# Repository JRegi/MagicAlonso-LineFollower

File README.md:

# MagicAlonso - _Robot dedicado a la leyenda Asturiana del automobilismo_

## MagicAlonso V1 (sin turbina)

## Descripción

_MagicAlonso_ es un robot seguidor de líneas de alto rendimiento con tracción y succión brushless.

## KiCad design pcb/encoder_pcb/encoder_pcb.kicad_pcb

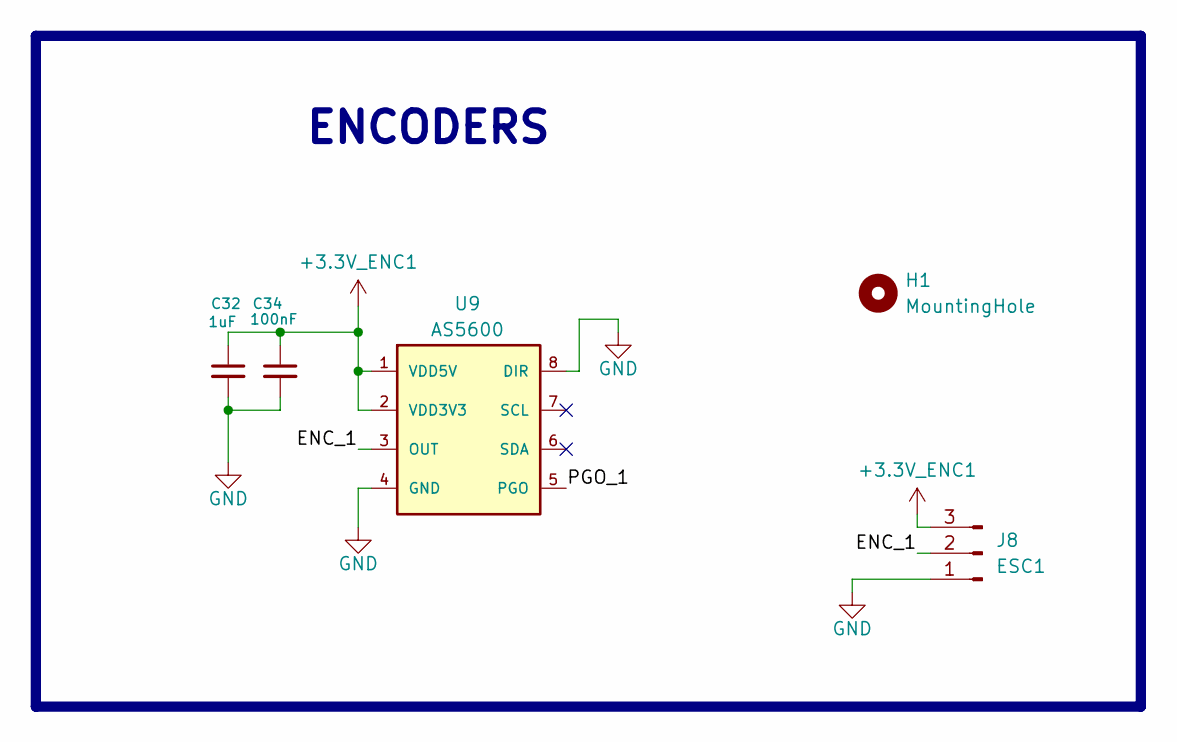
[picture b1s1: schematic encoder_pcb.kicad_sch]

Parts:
C32: 1uF; C_0603_1608Metric
C34: 100nF; C_0603_1608Metric
H1: MountingHole; MountingHole_2.2mm_M2
J8: ESC1; PinHeader_1x03_P2.54-SMD,THT,2-layers
U9: AS5600; SOIC-8_3.9x4.9mm_P1.27mm

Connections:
+3.3V_ENC1: C32.1, C34.1, J8.3, U9.1 (VDD5V), U9.2 (VDD3V3)
/ENC_1: J8.2, U9.3 (OUT)
/PGO_1: U9.5 (PGO)
GND: C32.2, C34.2, J8.1, U9.4 (GND), U9.8 (DIR)

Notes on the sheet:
ENCODERS

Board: 2 copper layers, 5 parts (0 on the bottom side), 3 nets, no tracks yet.

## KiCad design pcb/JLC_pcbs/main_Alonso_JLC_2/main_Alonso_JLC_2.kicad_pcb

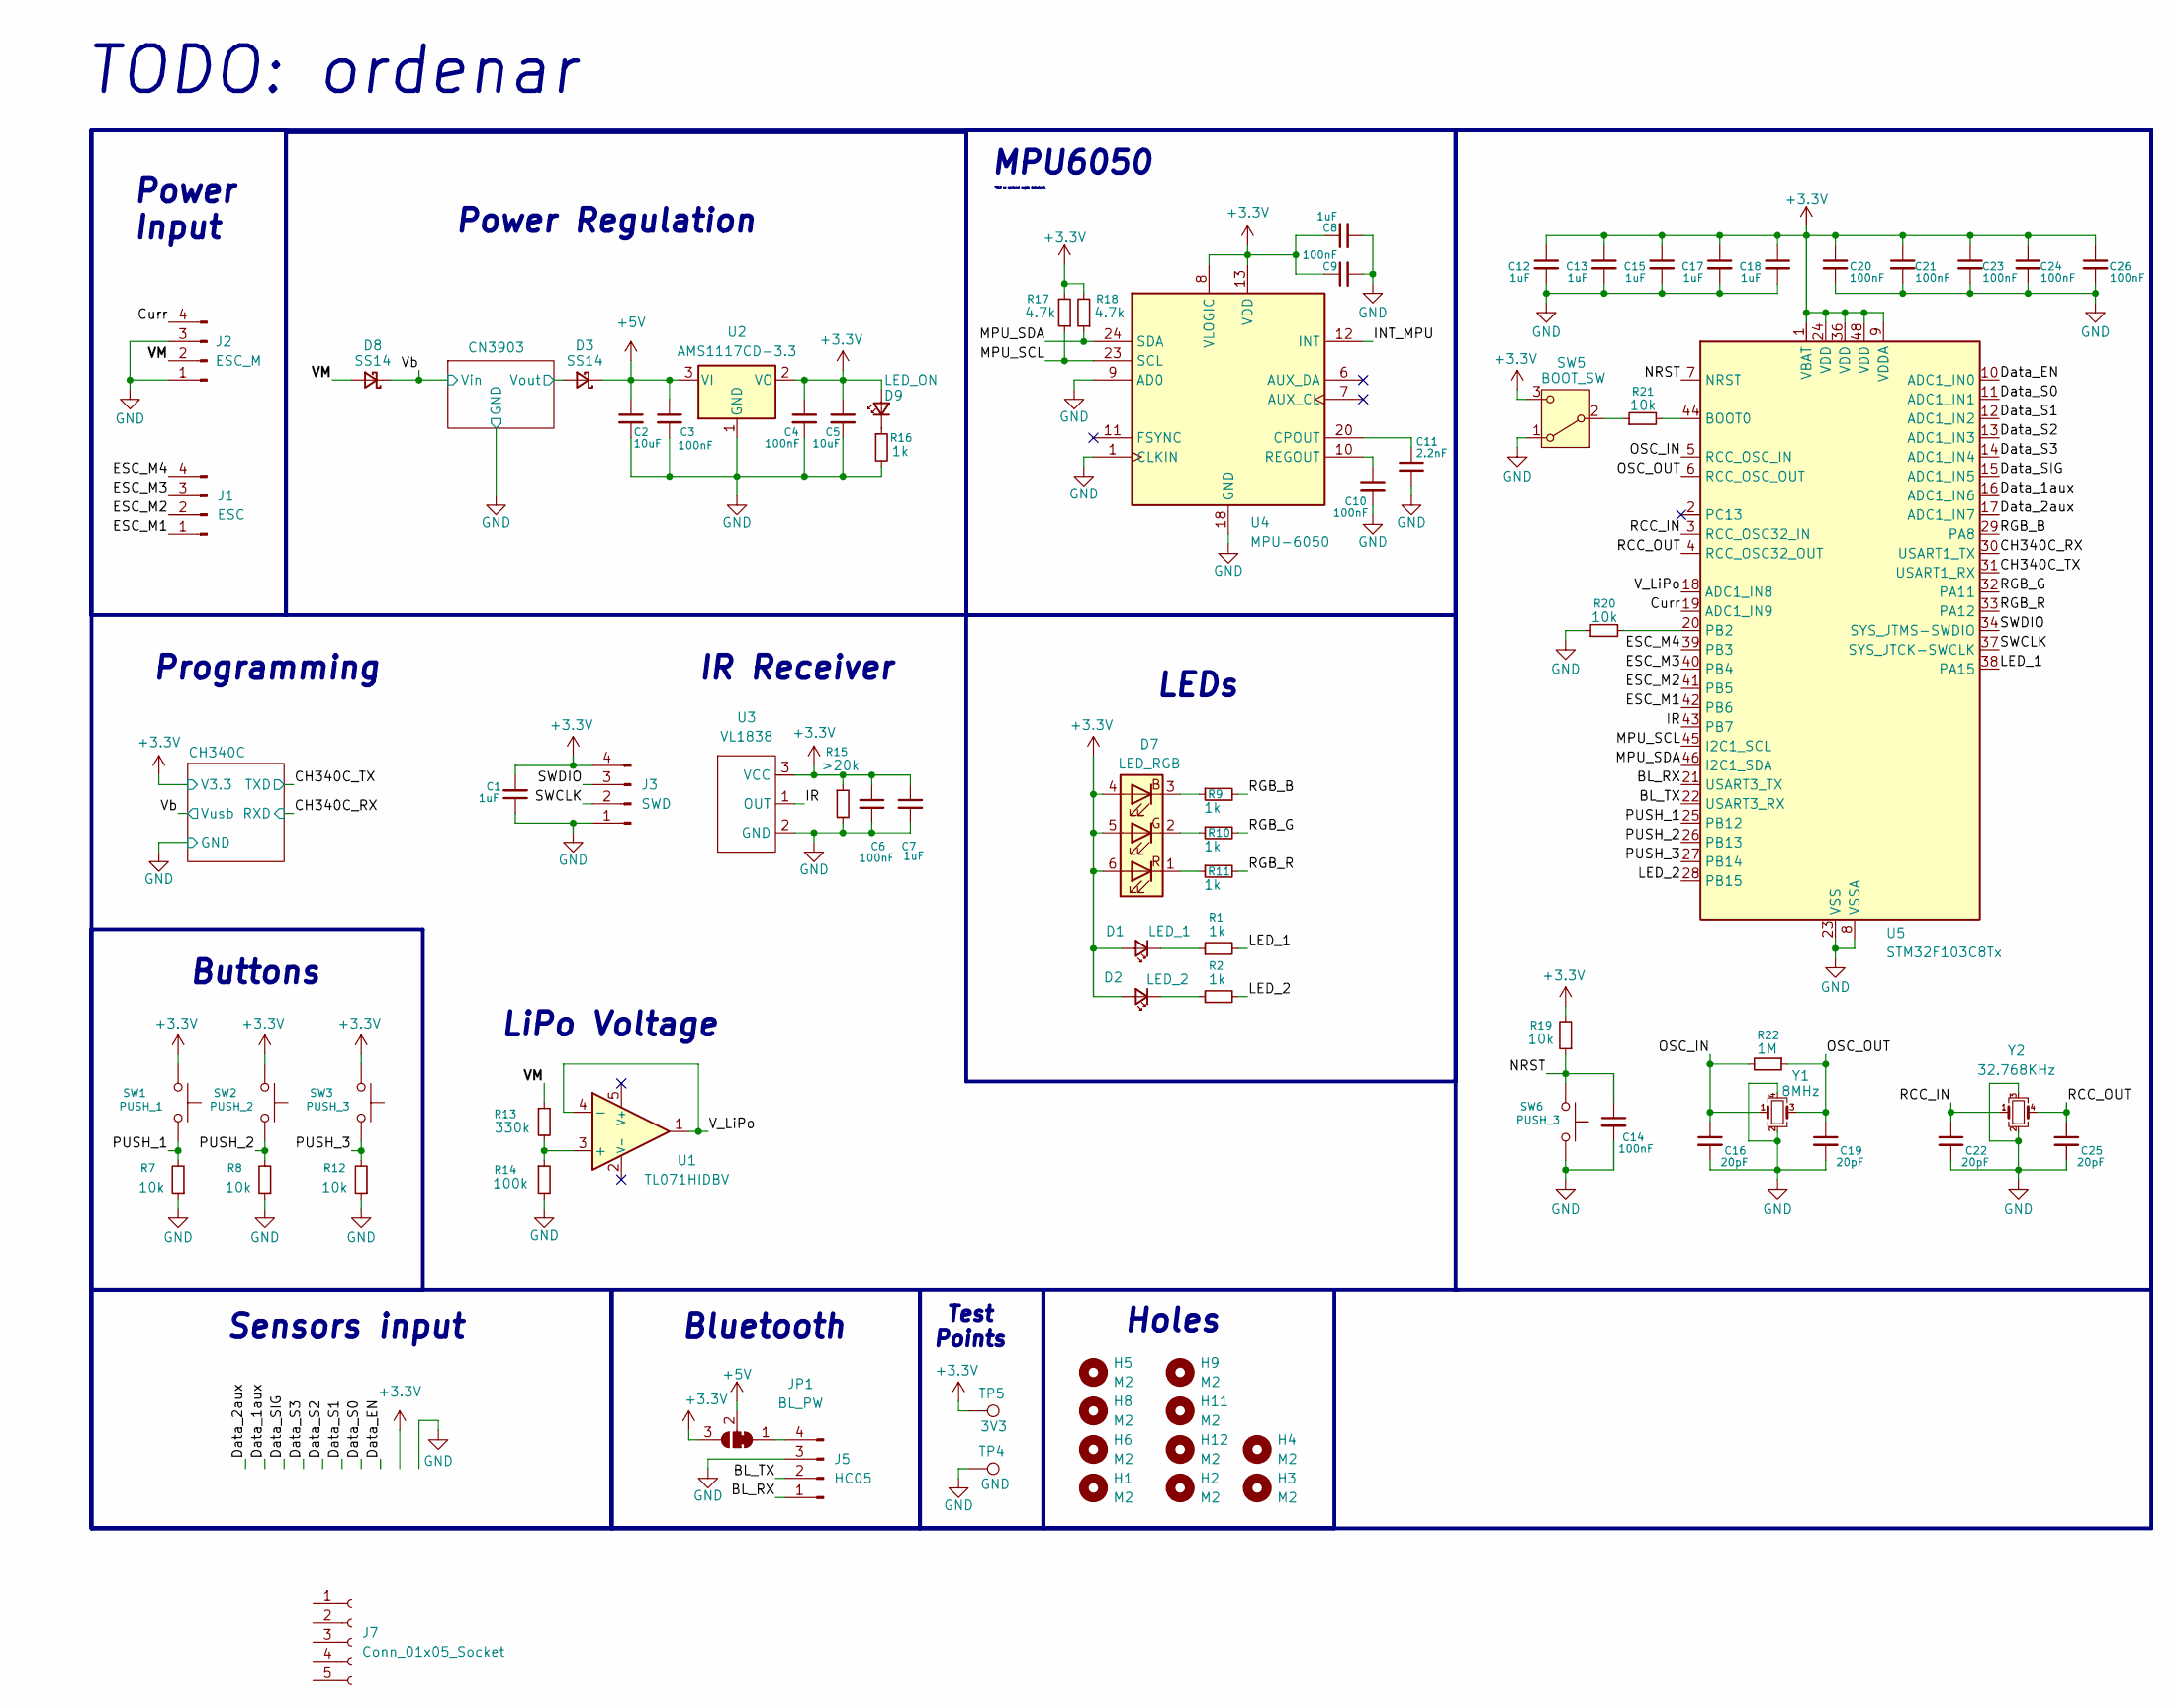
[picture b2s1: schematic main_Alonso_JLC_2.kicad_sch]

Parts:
C1, C12, C13, C15, C17, C18: 1uF; C_0805_2012Metric
C2, C5: 10uF; C_0805_2012Metric
C3, C4, C6, C9, C10, C14, C20, C21, C23, C24, C26: 100nF; C_0603_1608Metric
C7, C8: 1uF; C_0603_1608Metric
C11: 2.2nF; C_0603_1608Metric
C16, C19, C22, C25: 20pF; C_0603_1608Metric
D1: LED_1; LED_0805_2012Metric
D2: LED_2; LED_0805_2012Metric
D3, D8: SS14; D_SMA
D7: LED_RGB; LED_RGB_5050-6
D9: LED_ON; LED_0805_2012Metric
H1, H2, H3, H4, H5, H6, H8, H9, H11, H12: M2; MountingHole_2.2mm_M2
J1: ESC; pad_smd_x4
J2: ESC_M; pad_smd_x4
J3: SWD; JST_XH_B4B-XH-A_1x04_P2.50mm_Vertical
J5: HC05; PinSocket_1x04_P2.54mm_Vertical
J7: Conn_01x05_Socket
JP1: BL_PW; SolderJumper-3_P1.3mm_Bridged123_RoundedPad1.0x1.5mm
R1, R2, R9, R10, R11, R16: 1k; R_0603_1608Metric
R7, R8, R12, R19, R20, R21: 10k; R_0603_1608Metric
R13: 330k; R_0805_2012Metric
R14: 100k; R_0805_2012Metric
R15: >20k; R_0805_2012Metric
R17, R18: 4.7k; R_0603_1608Metric
R22: 1M; R_0603_1608Metric
SW1: PUSH_1; SW_Push_Sw-3424p_Handsolder
SW2: PUSH_2; SW_Push_Sw-3424p_Handsolder
SW3, SW6: PUSH_3; SW_Push_Sw-3424p_Handsolder
SW5: BOOT_SW; SW_DPDT_SLIDE_THT
TP4: GND; TestPoint_Pad_D1.5mm
TP5: 3V3; TestPoint_Pad_D1.5mm
U1: TL071HIDBV; SOT-23-5
U2: AMS1117CD-3.3; TO-252-3_TabPin2
U3: VL1838; JSumo_Microstart
U4: MPU-6050; InvenSense_QFN-24_4x4mm_P0.5mm
U5: STM32F103C8Tx; LQFP-48_7x7mm_P0.5mm
Y1: 8MHz; Crystal_SMD_5032-4Pin_5.0x3.2mm
Y2: 32.768KHz; Crystal_SMD_Abracon_ABS25-4Pin_8.0x3.8mm

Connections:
+3.3V: C1.2, C4.1, C5.1, C6.1, C7.1, C8.1, C9.1, C12.1, C13.1, C15.1, C17.1, C18.1, C20.1, C21.1, C23.1, C24.1, C26.1, D1.2 (A), D2.2 (A), D7.4 (BA), D7.5 (GA), D7.6 (RA), D9.2 (A), J3.4, JP1.3 (B), R15.1, R17.2, R18.2, R19.2, SW1.1, SW2.1, SW3.1, SW5.3 (C), TP5.1, U2.2 (VO), U3.3 (VCC), U4.8 (VLOGIC), U4.13 (VDD), U5.1 (VBAT), U5.9 (VDDA), U5.24 (VDD), U5.36 (VDD), U5.48 (VDD); also elsewhere on the board
+5V: C2.1, C3.1, D3.1 (K), JP1.2 (C), U2.3 (VI)
/BL_RX: J5.1, U5.21 (USART3_TX)
/BL_TX: J5.2, U5.22 (USART3_RX)
/CH340C_RX: U5.30 (USART1_TX); also elsewhere on the board
/CH340C_TX: U5.31 (USART1_RX); also elsewhere on the board
/CN3903/Vsw: D3.2 (A); also elsewhere on the board
/Curr: J2.4, U5.19 (ADC1_IN9)
/Data_1aux: U5.16 (ADC1_IN6); also elsewhere on the board
/Data_2aux: U5.17 (ADC1_IN7); also elsewhere on the board
/Data_EN: U5.10 (ADC1_IN0); also elsewhere on the board
/Data_S0: U5.11 (ADC1_IN1); also elsewhere on the board
/Data_S1: U5.12 (ADC1_IN2); also elsewhere on the board
/Data_S2: U5.13 (ADC1_IN3); also elsewhere on the board
/Data_S3: U5.14 (ADC1_IN4); also elsewhere on the board
/Data_SIG: U5.15 (ADC1_IN5); also elsewhere on the board
/ESC_M1: J1.1, U5.42 (PB6)
/ESC_M2: J1.2, U5.41 (PB5)
/ESC_M3: J1.3, U5.40 (PB4)
/ESC_M4: J1.4, U5.39 (PB3)
/INT_MPU: U4.12 (INT)
/IR: U3.1 (OUT), U5.43 (PB7)
/LED_1: R1.2, U5.38 (PA15)
/LED_2: R2.2, U5.28 (PB15)
/MPU_SCL: R17.1, U4.23 (SCL), U5.45 (I2C1_SCL)
/MPU_SDA: R18.1, U4.24 (SDA), U5.46 (I2C1_SDA)
/NRST: C14.1, R19.1, SW6.1, U5.7 (NRST)
/OSC_IN: C16.1, R22.2, U5.5 (RCC_OSC_IN), Y1.1
/OSC_OUT: C19.1, R22.1, U5.6 (RCC_OSC_OUT), Y1.3
/PUSH_1: R7.2, SW1.2, U5.25 (PB12)
/PUSH_2: R8.2, SW2.2, U5.26 (PB13)
/PUSH_3: R12.2, SW3.2, U5.27 (PB14)
/RCC_IN: C22.1, U5.3 (RCC_OSC32_IN), Y2.1
/RCC_OUT: C25.1, U5.4 (RCC_OSC32_OUT), Y2.4
/RGB_B: R9.2, U5.29 (PA8)
/RGB_G: R10.2, U5.32 (PA11)
/RGB_R: R11.2, U5.33 (PA12)
/SWCLK: J3.2, U5.37 (SYS_JTCK-SWCLK)
/SWDIO: J3.3, U5.34 (SYS_JTMS-SWDIO)
/VM: D8.2 (A), J2.2, R13.1
/V_LiPo: U1.1, U1.4 (-), U5.18 (ADC1_IN8)
/Vb: D8.1 (K); also elsewhere on the board
GND: C1.1, C2.2, C3.2, C4.2, C5.2, C6.2, C7.2, C8.2, C9.2, C10.2, C11.2, C12.2, C13.2, C14.2, C15.2, C16.2, C17.2, C18.2, C19.2, C20.2, C21.2, C22.2, C23.2, C24.2, C25.2, C26.2, J2.1, J2.3, J3.1, J5.3, R7.1, R8.1, R12.1, R14.2, R15.2, R16.2, R20.1, SW5.1 (A), SW6.2, TP4.1, U2.1 (GND), U3.2 (GND), U4.1 (CLKIN), U4.9 (AD0), U4.18 (GND), U5.8 (VSSA), U5.23 (VSS), U5.35 (VSS), U5.47 (VSS), Y1.2, Y1.4, Y2.2, Y2.3; also elsewhere on the board
unnamed: D1.1 (K), R1.1
unnamed: D2.1 (K), R2.1
unnamed: D7.3 (BK), R9.1
unnamed: D7.2 (GK), R10.1
unnamed: D7.1 (RK), R11.1
unnamed: D9.1 (K), R16.1
unnamed: J5.4, JP1.1 (A)
unnamed: R21.1, SW5.2 (B)
unnamed: R13.2, R14.1, U1.3 (+)
unnamed: C11.1, U4.20 (CPOUT)
unnamed: C10.1, U4.10 (REGOUT)
unnamed: R21.2, U5.44 (BOOT0)
unnamed: R20.2, U5.20 (PB2)

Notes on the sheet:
Sensors input
TODO: ordenar
MPU6050
Power Input
Test Points
Holes
*R19 es opcional según datasheet.
Power Regulation
Programming
Buttons
Bluetooth
LEDs
LiPo Voltage
IR Receiver

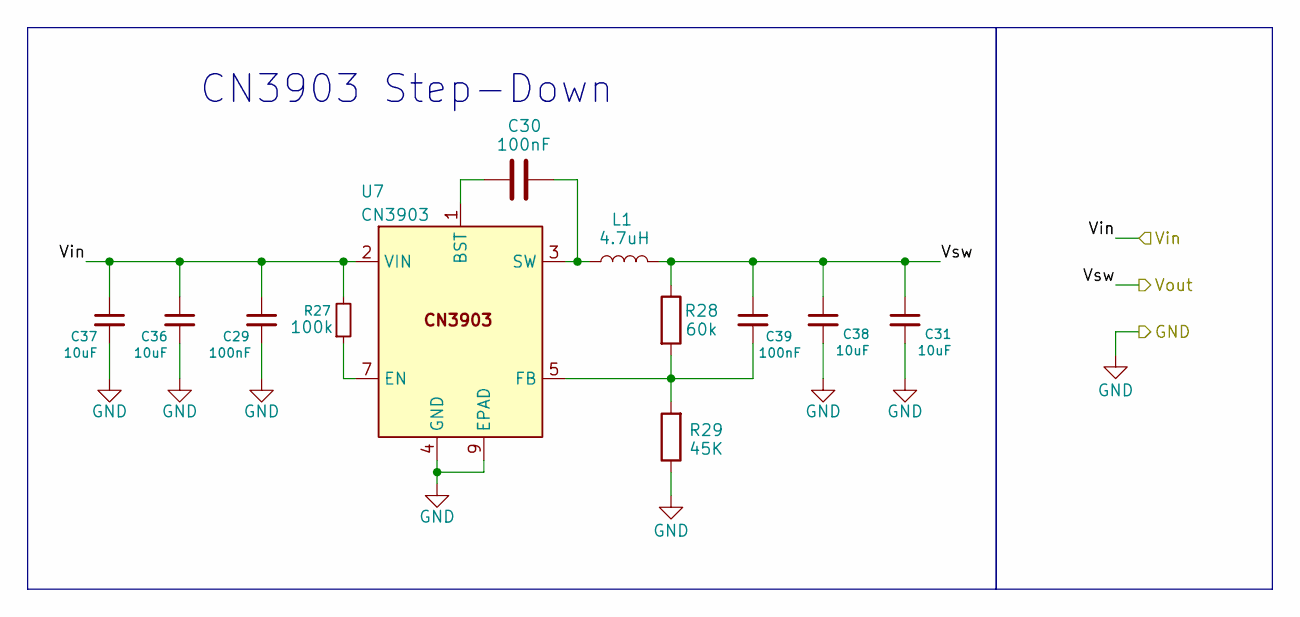
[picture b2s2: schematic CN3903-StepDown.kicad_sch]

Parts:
C29: 100nF; C_0603_1608Metric
C30, C39: 100nF; C_0402_1005Metric_Pad0.74x0.62mm_HandSolder
C31, C38: 10uF; C_0805_2012Metric
C36, C37: 10uF; C_0603_1608Metric
L1: 4.7uH; L_Wuerth_HCM-7050
R27: 100k; R_0603_1608Metric
R28: 60k; R_0402_1005Metric_Pad0.72x0.64mm_HandSolder
R29: 45K; R_0402_1005Metric_Pad0.72x0.64mm_HandSolder
U7: CN3903; SOIC-8-1EP_3.9x4.9mm_P1.27mm_EP2.41x3.3mm_ThermalVias

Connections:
/CN3903/Vsw: C31.1, C38.1, C39.1, L1.2, R28.1; also elsewhere on the board
/Vb: C29.1, C36.1, C37.1, R27.2, U7.2 (VIN); also elsewhere on the board
GND: C29.2, C31.2, C36.2, C37.2, C38.2, R29.1, U7.4 (GND), U7.9 (EPAD); also elsewhere on the board
unnamed: C30.1, U7.1 (BST)
unnamed: R27.1, U7.7 (EN)
unnamed: C39.2, R28.2, R29.2, U7.5 (FB)
unnamed: C30.2, L1.1, U7.3 (SW)

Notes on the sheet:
CN3903 Step-Down

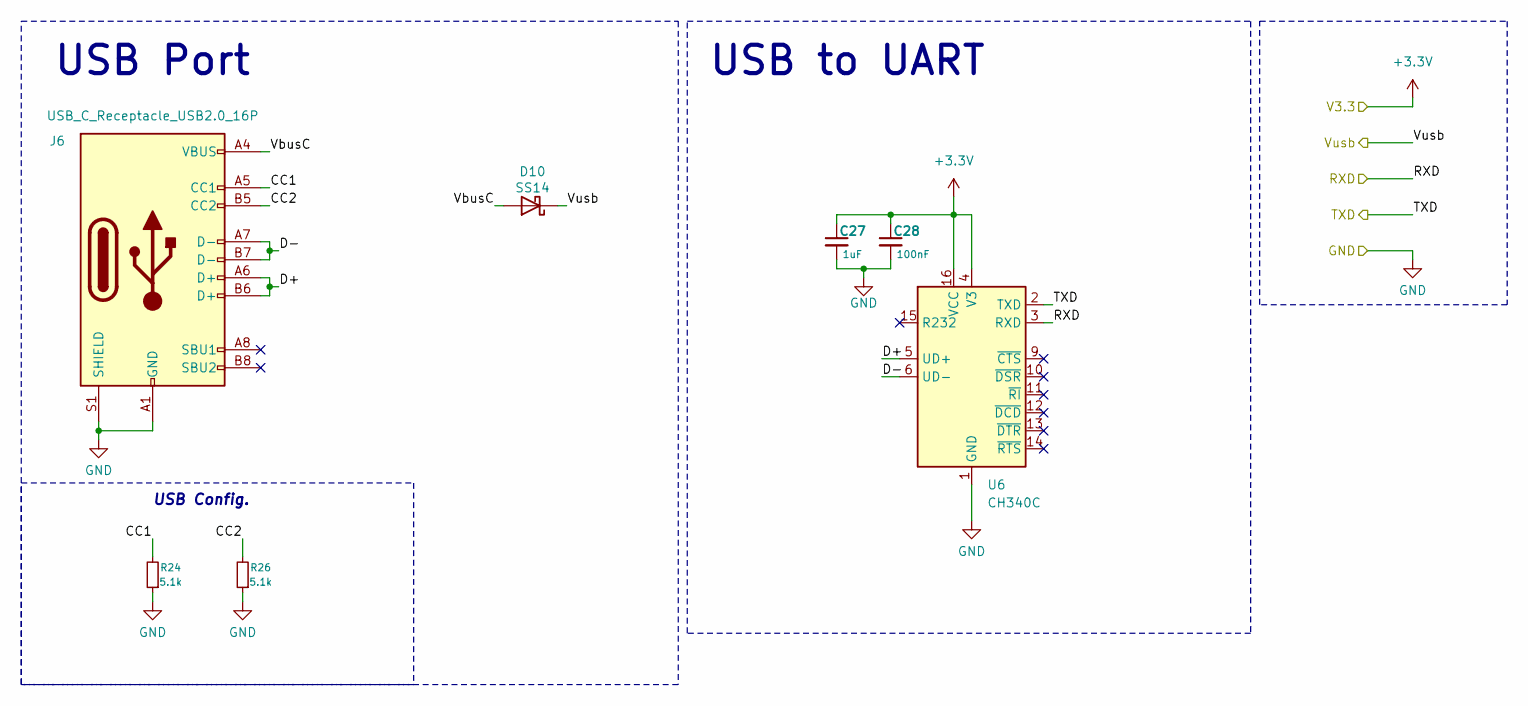
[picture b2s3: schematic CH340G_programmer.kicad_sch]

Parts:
C27: 1uF; C_0805_2012Metric
C28: 100nF; C_0603_1608Metric
D10: SS14; D_SOD-123
J6: USB_C_Receptacle_USB2.0_16P; USB_C_Receptacle_GCT_USB4110
R24, R26: 5.1k; R_0603_1608Metric
U6: CH340C; SOIC-16_3.9x9.9mm_P1.27mm

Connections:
+3.3V: C27.1, C28.1, U6.4 (V3), U6.16 (VCC); also elsewhere on the board
/CH340C/CC1: J6.A5 (CC1), R24.2
/CH340C/CC2: J6.B5 (CC2), R26.2
/CH340C/D+: J6.A6 (D+), J6.B6 (D+), U6.5 (UD+)
/CH340C/D-: J6.A7 (D-), J6.B7 (D-), U6.6 (UD-)
/CH340C/VbusC: D10.2 (A), J6.A4 (VBUS), J6.A9 (VBUS), J6.B4 (VBUS), J6.B9 (VBUS)
/CH340C_RX: U6.3 (RXD); also elsewhere on the board
/CH340C_TX: U6.2 (TXD); also elsewhere on the board
/Vb: D10.1 (K); also elsewhere on the board
GND: C27.2, C28.2, J6.A1 (GND), J6.A12 (GND), J6.B1 (GND), J6.B12 (GND), J6.S1 (SHIELD), R24.1, R26.1, U6.1 (GND); also elsewhere on the board

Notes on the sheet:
USB to UART
USB Config.
USB Port

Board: 2 copper layers, 99 parts (0 on the bottom side), 64 nets, no tracks yet.

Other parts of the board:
J4: Sensors; JST_XH_S10B-XH-A_1x10_P2.50mm_Horizontal

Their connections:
+3.3V: J4.9; also elsewhere on the board
/Data_1aux: J4.2; also elsewhere on the board
/Data_2aux: J4.1; also elsewhere on the board
/Data_EN: J4.8; also elsewhere on the board
/Data_S0: J4.7; also elsewhere on the board
/Data_S1: J4.6; also elsewhere on the board
/Data_S2: J4.5; also elsewhere on the board
/Data_S3: J4.4; also elsewhere on the board
/Data_SIG: J4.3; also elsewhere on the board
GND: J4.10; also elsewhere on the board

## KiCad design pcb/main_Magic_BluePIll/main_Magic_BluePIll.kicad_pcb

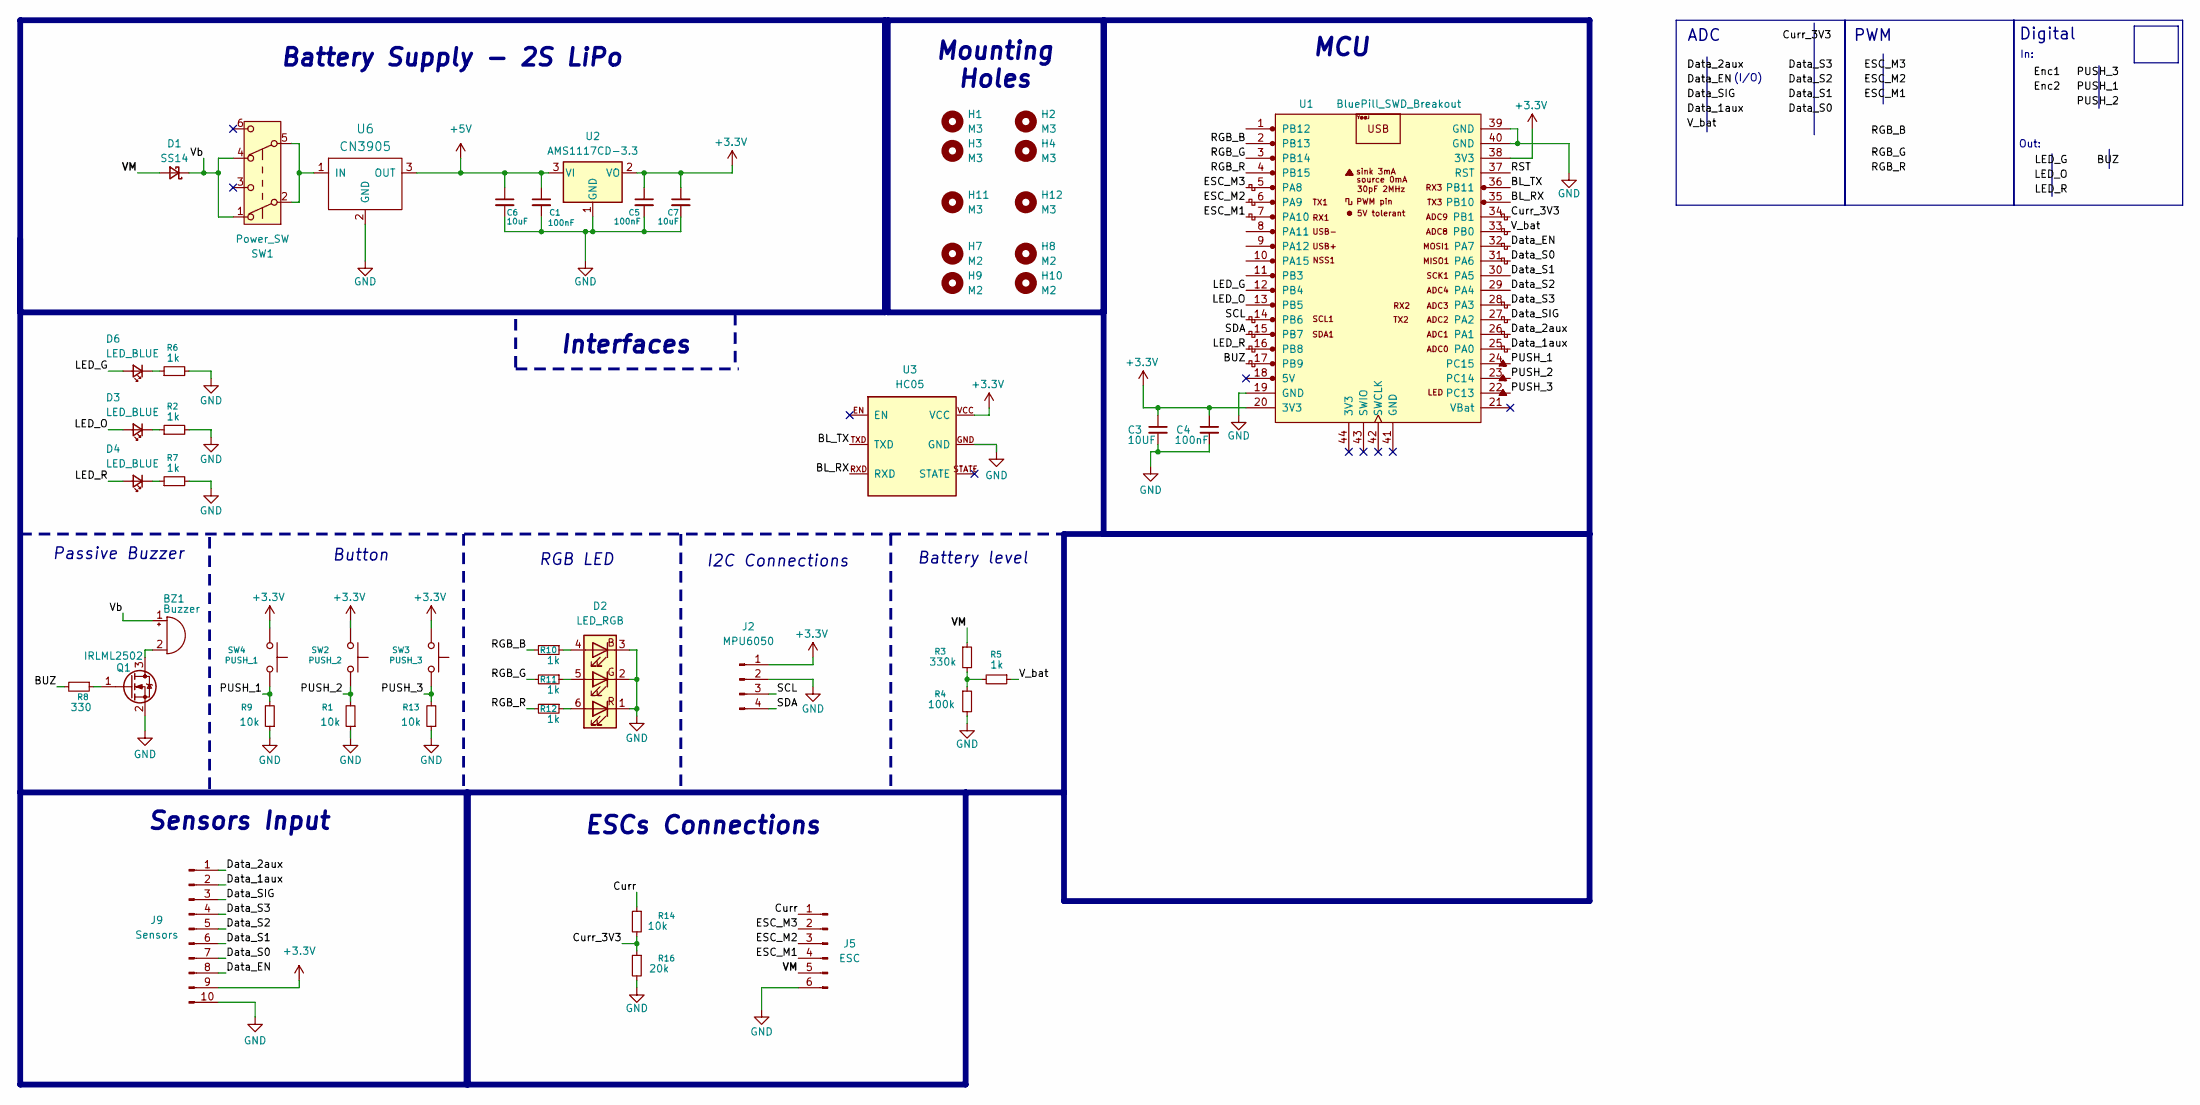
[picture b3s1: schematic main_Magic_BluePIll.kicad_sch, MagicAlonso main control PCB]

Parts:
BZ1: Buzzer; Buzzer_12x9.5RM7.6
C1, C5: 100nF; C_0603_1608Metric
C3: 10UF; C_0805_2012Metric
C4: 100nF; C_0805_2012Metric
C6, C7: 10uF; C_0805_2012Metric
D1: SS14; D_SOD-123
D2: LED_RGB; LED_RGB_5050-6
D3, D4, D6: LED_BLUE; LED_0805_2012Metric
H1, H2, H3, H4, H11, H12: M3; MountingHole_3mm
H7, H8, H9, H10: M2; MountingHole_2.2mm_M2
J2: MPU6050; MPU6050_Module
J5: ESC; JST_XH_B6B-XH-A_1x06_P2.50mm_Vertical
J9: Sensors; JST_XH_S10B-XH-A_1x10_P2.50mm_Horizontal
Q1: IRLML2502; SOT-23
R1, R9, R13: 10k; R_0603_1608Metric
R2, R6, R7, R10, R11, R12: 1k; R_0603_1608Metric
R3: 330k; R_0805_2012Metric
R4: 100k; R_0805_2012Metric
R5: 1k; R_0805_2012Metric
R8: 330; R_0805_2012Metric
R14: 10k; R_0805_2012Metric
R16: 20k; R_0805_2012Metric
SW1: Power_SW; SW_DPDT_SLIDE_THT
SW2: PUSH_2; SW_Push_Sw-3424p_Handsolder
SW3: PUSH_3; SW_Push_Sw-3424p_Handsolder
SW4: PUSH_1; SW_Push_Sw-3424p_Handsolder
U1: BluePill_SWD_Breakout; BluePill
U2: AMS1117CD-3.3; TO-252-3_TabPin2
U3: HC05
U6: CN3905; Mini360_step-down

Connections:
+3.3V: C3.1, C4.1, C5.1, C7.1, J2.1, J9.9, SW2.1, SW3.1, SW4.1, U1.20 (3V3), U1.38 (3V3), U2.2 (VO), U3.VCC
+5V: C1.1, C6.1, U2.3 (VI), U6.3 (OUT)
/BL_RX: U1.35 (PB10), U3.RXD
/BL_TX: U1.36 (PB11), U3.TXD
/BUZ: R8.2, U1.17 (PB9)
/Curr: J5.1, R14.1
/Curr_3V3: R14.2, R16.1, U1.34 (PB1)
/Data_1aux: J9.2, U1.25 (PA0)
/Data_2aux: J9.1, U1.26 (PA1)
/Data_EN: J9.8, U1.32 (PA7)
/Data_S0: J9.7, U1.31 (PA6)
/Data_S1: J9.6, U1.30 (PA5)
/Data_S2: J9.5, U1.29 (PA4)
/Data_S3: J9.4, U1.28 (PA3)
/Data_SIG: J9.3, U1.27 (PA2)
/ESC_M1: J5.4, U1.7 (PA10)
/ESC_M2: J5.3, U1.6 (PA9)
/ESC_M3: J5.2, U1.5 (PA8)
/LED_G: D6.2 (A), U1.12 (PB4)
/LED_O: D3.2 (A), U1.13 (PB5)
/LED_R: D4.2 (A), U1.16 (PB8)
/PUSH_1: R9.2, SW4.2, U1.24 (PC15)
/PUSH_2: R1.2, SW2.2, U1.23 (PC14)
/PUSH_3: R13.2, SW3.2, U1.22 (PC13)
/RGB_B: R10.2, U1.2 (PB13)
/RGB_G: R11.2, U1.3 (PB14)
/RGB_R: R12.2, U1.4 (PB15)
/RST: U1.37 (RST)
/SCL: J2.3, U1.14 (PB6)
/SDA: J2.4, U1.15 (PB7)
/VM: D1.2 (A), J5.5, R3.1
/V_bat: R5.1, U1.33 (PB0)
/Vb: BZ1.1 (+), D1.1 (K), SW1.1 (A), SW1.4 (A)
GND: C1.2, C3.2, C4.2, C5.2, C6.2, C7.2, D2.1 (RK), D2.2 (GK), D2.3 (BK), J2.2, J5.6, J9.10, Q1.2 (S), R1.1, R2.2, R4.2, R6.2, R7.2, R9.1, R13.1, R16.2, U1.19 (GND), U1.39 (GND), U1.40 (GND), U2.1 (GND), U3.GND, U6.2 (GND)
unnamed: BZ1.2 (-), Q1.3 (D)
unnamed: D2.4 (BA), R10.1
unnamed: D2.5 (GA), R11.1
unnamed: D2.6 (RA), R12.1
unnamed: D3.1 (K), R2.1
unnamed: D4.1 (K), R7.1
unnamed: D6.1 (K), R6.1
unnamed: Q1.1 (G), R8.1
unnamed: R3.2, R4.1, R5.2
unnamed: SW1.2 (B), SW1.5 (B), U6.1 (IN)

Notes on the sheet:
Out:
(I/O)
Passive Buzzer
Digital
Battery level
I2C Connections
Mounting Holes
Battery Supply - 2S LiPo
In:
Sensors Input
MCU
ESCs Connections
PWM
RGB LED
Button
Interfaces
ADC

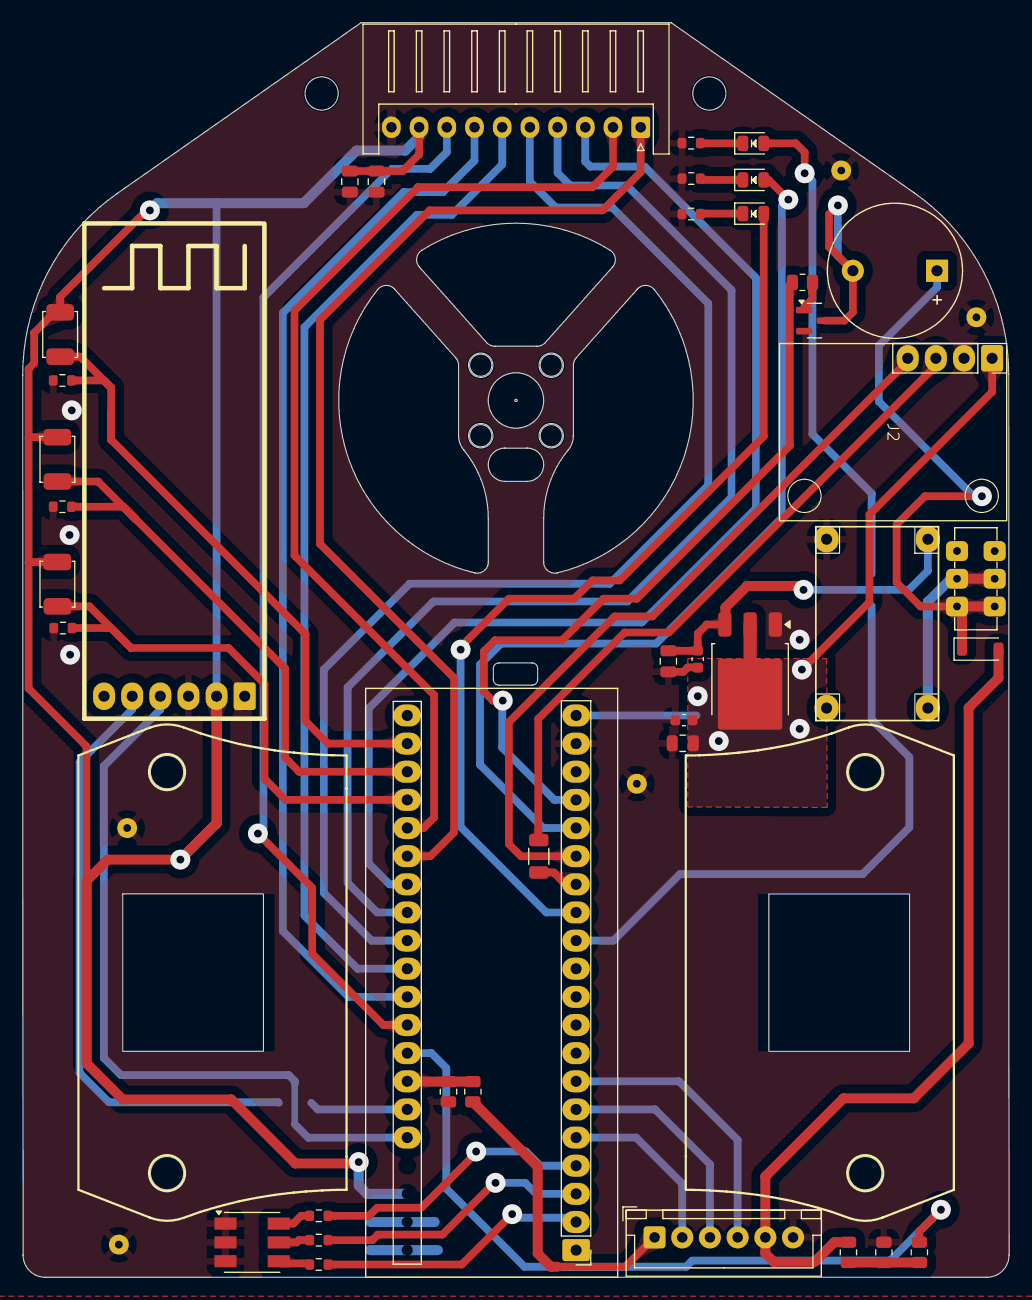
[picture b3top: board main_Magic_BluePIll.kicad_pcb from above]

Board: 2 copper layers, 89.0 x 113.2 mm, 49 parts (0 on the bottom side), 43 nets.

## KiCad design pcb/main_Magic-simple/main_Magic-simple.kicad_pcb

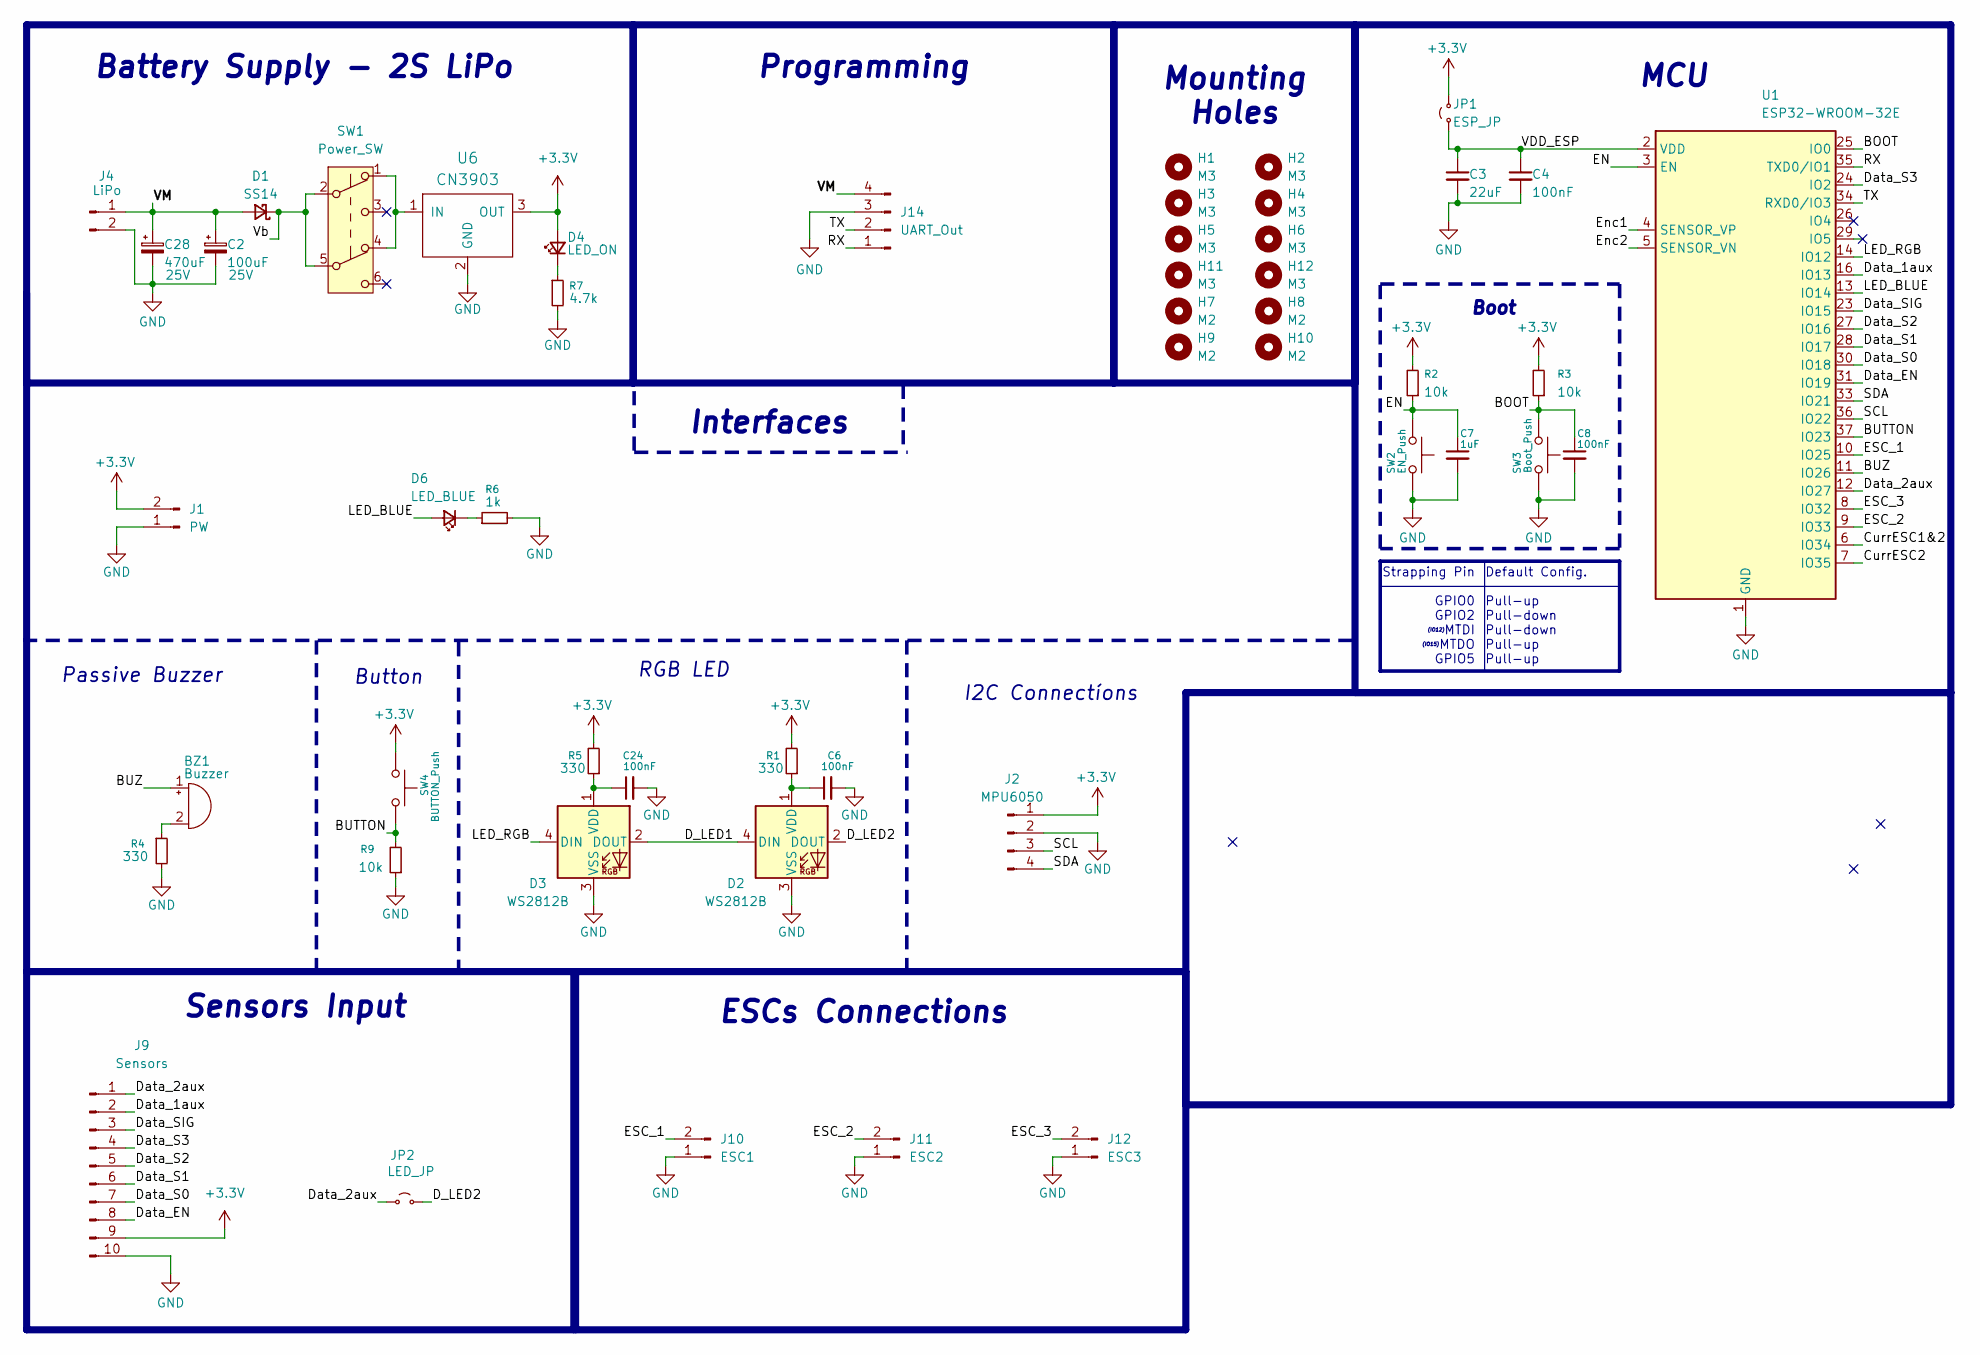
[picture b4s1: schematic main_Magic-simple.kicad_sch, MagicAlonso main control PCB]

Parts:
BZ1: Buzzer; Buzzer_12x9.5RM7.6
C2: 100uF; CP_Radial_D8.0mm_P3.50mm
C3: 22uF; C_0805_2012Metric
C4, C6, C24: 100nF; C_0805_2012Metric
C7: 1uF; C_0805_2012Metric
C8: 100nF; C_0603_1608Metric
C28: 470uF; CP_Radial_D8.0mm_P3.50mm
D1: SS14; D_SMA
D2, D3: WS2812B; LED_WS2812B_PLCC4_5.0x5.0mm_P3.2mm
D4: LED_ON; LED_0805_2012Metric
D6: LED_BLUE; LED_0805_2012Metric
H1, H2, H3, H4, H5, H6, H11, H12: M3; MountingHole_3mm
H7, H8, H9, H10: M2; MountingHole_2.2mm_M2
J1: PW; JST_XH_B2B-XH-A_1x02_P2.50mm_Vertical
J2: MPU6050; MPU6050_Module
J4: LiPo; JST_XH_S2B-XH-A_1x02_P2.50mm_Horizontal
J9: Sensors; JST_XH_S10B-XH-A_1x10_P2.50mm_Horizontal
J10: ESC1; JST_XH_S2B-XH-A_1x02_P2.50mm_Horizontal
J11: ESC2; JST_XH_S2B-XH-A_1x02_P2.50mm_Horizontal
J12: ESC3; JST_XH_S2B-XH-A_1x02_P2.50mm_Horizontal
J14: UART_Out; JST_XH_S4B-XH-A_1x04_P2.50mm_Horizontal
JP1: ESP_JP; R_1206_3216Metric
JP2: LED_JP; R_1206_3216Metric
R1, R4, R5: 330; R_0805_2012Metric
R2, R3: 10k; R_0603_1608Metric
R6: 1k; R_0603_1608Metric
R7: 4.7k; R_0603_1608Metric
R9: 10k; R_0805_2012Metric
SW1: Power_SW; SW_Push_2P2T_Toggle_CK_PVA2OAH5xxxxxxV2
SW2: EN_Push; SW_Push_SPST_NO_Alps_SKRK_Handsolder
SW3: Boot_Push; SW_Push_SPST_NO_Alps_SKRK_Handsolder
SW4: BUTTON_Push; SW_SPST_CK_RS282G05A3
U1: ESP32-WROOM-32E
U6: CN3903; Mini360_step-down

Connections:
+3.3V: D4.2 (A), J1.2, J2.1, J9.9, JP1.2 (B), R1.2, R2.2, R3.2, R5.2, SW4.1, U6.3 (OUT)
/BOOT: C8.1, R3.1, SW3.1, U1.25 (IO0)
/BUTTON: R9.2, SW4.2, U1.37 (IO23)
/BUZ: BZ1.1 (+), U1.11 (IO26)
/CurrESC1&2: U1.6 (IO34)
/CurrESC2: U1.7 (IO35)
/D_LED1: D2.4 (DIN), D3.2 (DOUT)
/D_LED2: D2.2 (DOUT), JP2.2 (B)
/Data_1aux: J9.2, U1.16 (IO13)
/Data_2aux: J9.1, JP2.1 (A), U1.12 (IO27)
/Data_EN: J9.8, U1.31 (IO19)
/Data_S0: J9.7, U1.30 (IO18)
/Data_S1: J9.6, U1.28 (IO17)
/Data_S2: J9.5, U1.27 (IO16)
/Data_S3: J9.4, U1.24 (IO2)
/Data_SIG: J9.3, U1.23 (IO15)
/EN: C7.1, R2.1, SW2.1, U1.3 (EN)
/ESC_1: J10.2, U1.10 (IO25)
/ESC_2: J11.2, U1.9 (IO33)
/ESC_3: J12.2, U1.8 (IO32)
/Enc1: U1.4 (SENSOR_VP)
/Enc2: U1.5 (SENSOR_VN)
/LED_BLUE: D6.2 (A), U1.13 (IO14)
/LED_RGB: D3.4 (DIN), U1.14 (IO12)
/RX: J14.1, U1.35 (TXD0/IO1)
/SCL: J2.3, U1.36 (IO22)
/SDA: J2.4, U1.33 (IO21)
/TX: J14.2, U1.34 (RXD0/IO3)
/VDD_ESP: C3.1, C4.1, JP1.1 (A), U1.2 (VDD)
/VM: C2.1, C28.1, D1.2 (A), J4.1, J14.4
/Vb: D1.1 (K), SW1.2 (B), SW1.5 (B)
GND: C2.2, C3.2, C4.2, C6.2, C7.2, C8.2, C24.2, C28.2, D2.3 (VSS), D3.3 (VSS), J1.1, J2.2, J4.2, J9.10, J10.1, J11.1, J12.1, J14.3, R4.2, R6.2, R7.2, R9.1, SW2.2, SW3.2, U1.1 (GND), U1.15 (GND), U1.38 (GND), U1.39 (GND), U6.2 (GND)
unnamed: BZ1.2 (-), R4.1
unnamed: C6.1, D2.1 (VDD), R1.1
unnamed: C24.1, D3.1 (VDD), R5.1
unnamed: D4.1 (K), R7.1
unnamed: D6.1 (K), R6.1
unnamed: SW1.1 (A), SW1.4 (A), U6.1 (IN)

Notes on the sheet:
Strapping Pin GPIO0 GPIO2 MTDI MTDO GPIO5
(IO12)
Passive Buzzer
(IO15)
I2C Connectíons
Mounting Holes
Battery Supply - 2S LiPo
Sensors Input
MCU
ESCs Connections
Boot
RGB LED
Button
Interfaces
Default Config. Pull-up Pull-down Pull-down Pull-up Pull-up
Programming

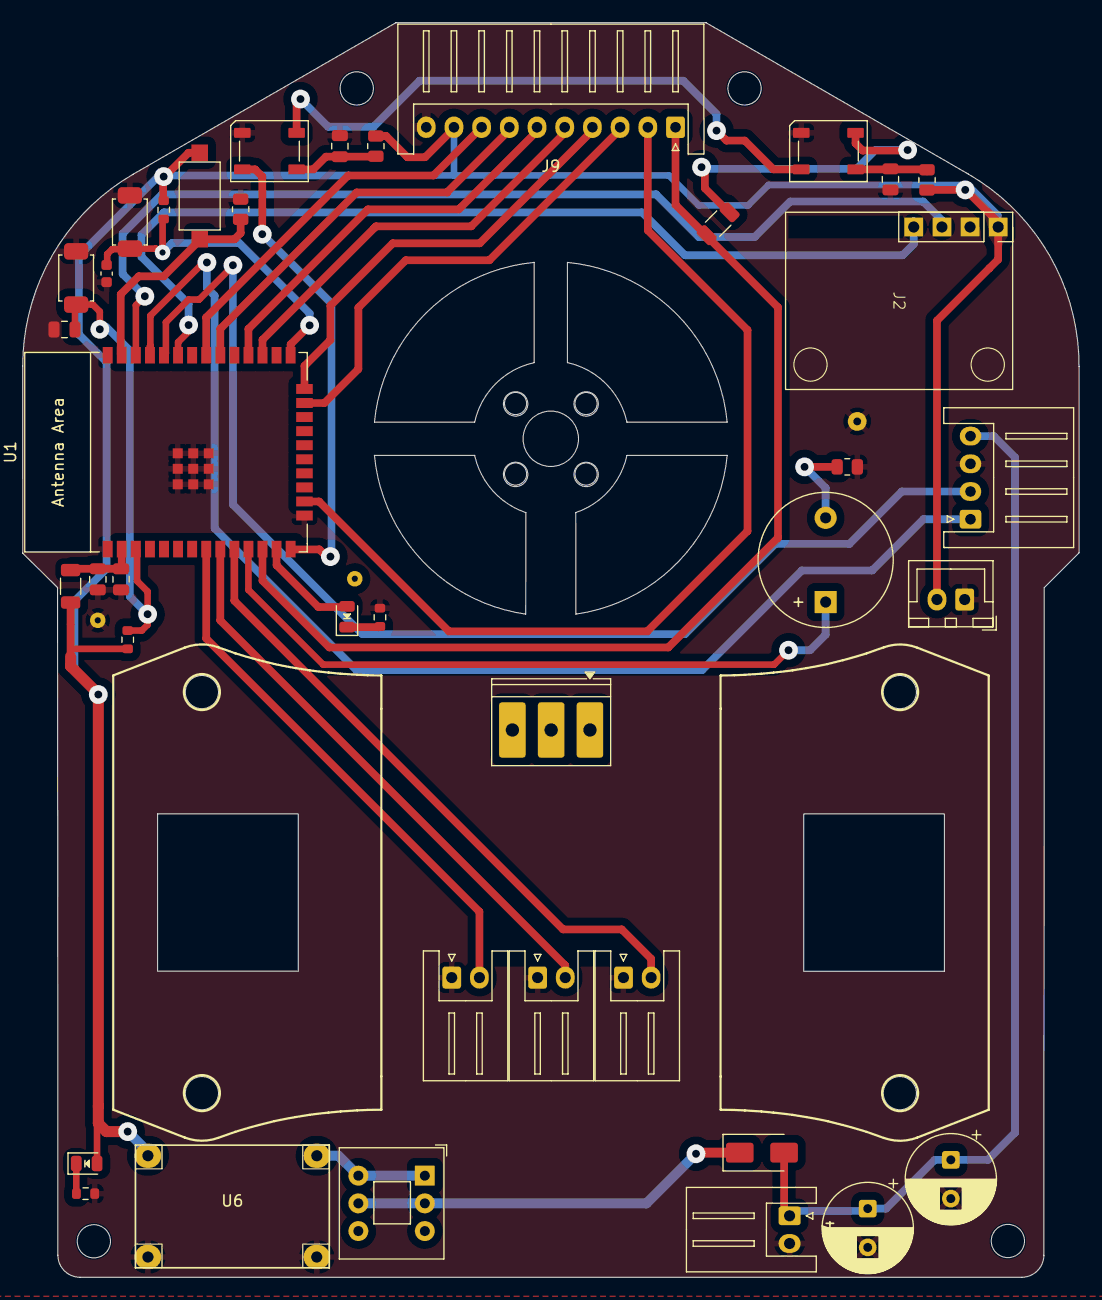
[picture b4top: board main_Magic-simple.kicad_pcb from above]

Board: 2 copper layers, 95.3 x 113.2 mm, 51 parts (0 on the bottom side), 34 nets.

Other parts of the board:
ESC_3: TerminalBlock_Phoenix_PT-1,5-3-3.5-H_1x03_P3.50mm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; TerminalBlock_Phoenix_PT-1,5-3-3.5-H_1x03_P3.50mm_Horizontal
